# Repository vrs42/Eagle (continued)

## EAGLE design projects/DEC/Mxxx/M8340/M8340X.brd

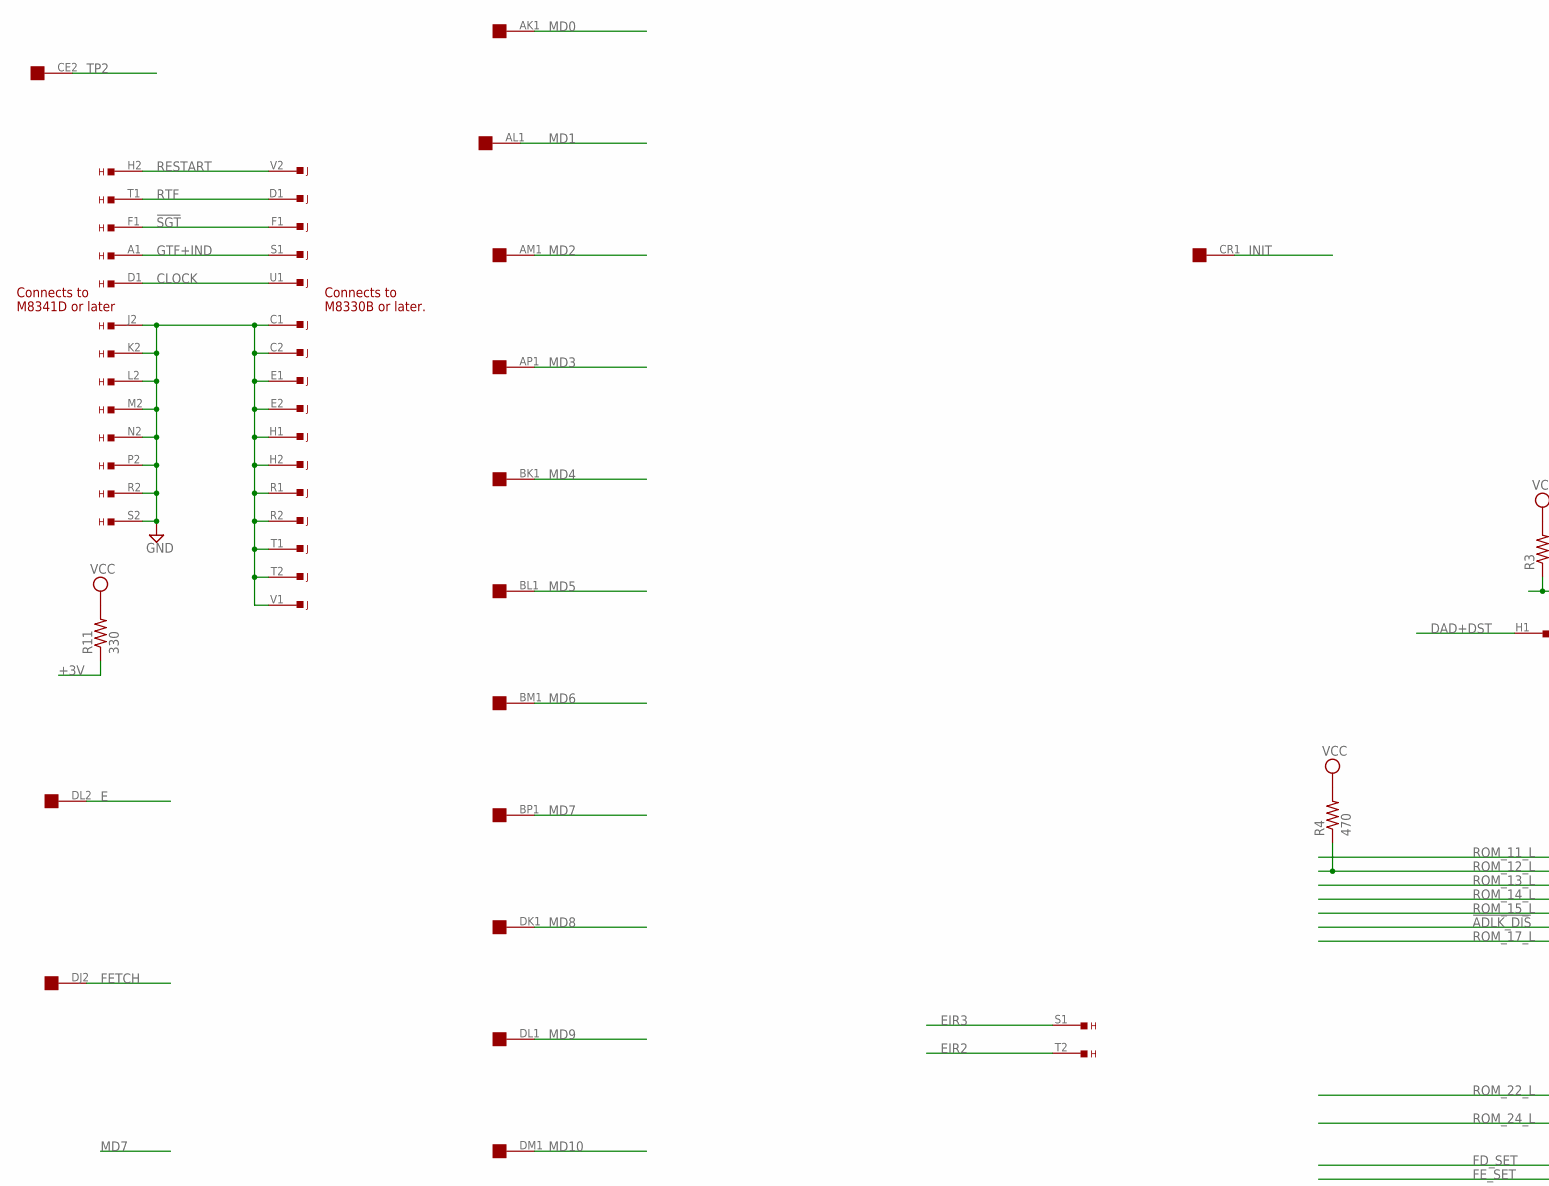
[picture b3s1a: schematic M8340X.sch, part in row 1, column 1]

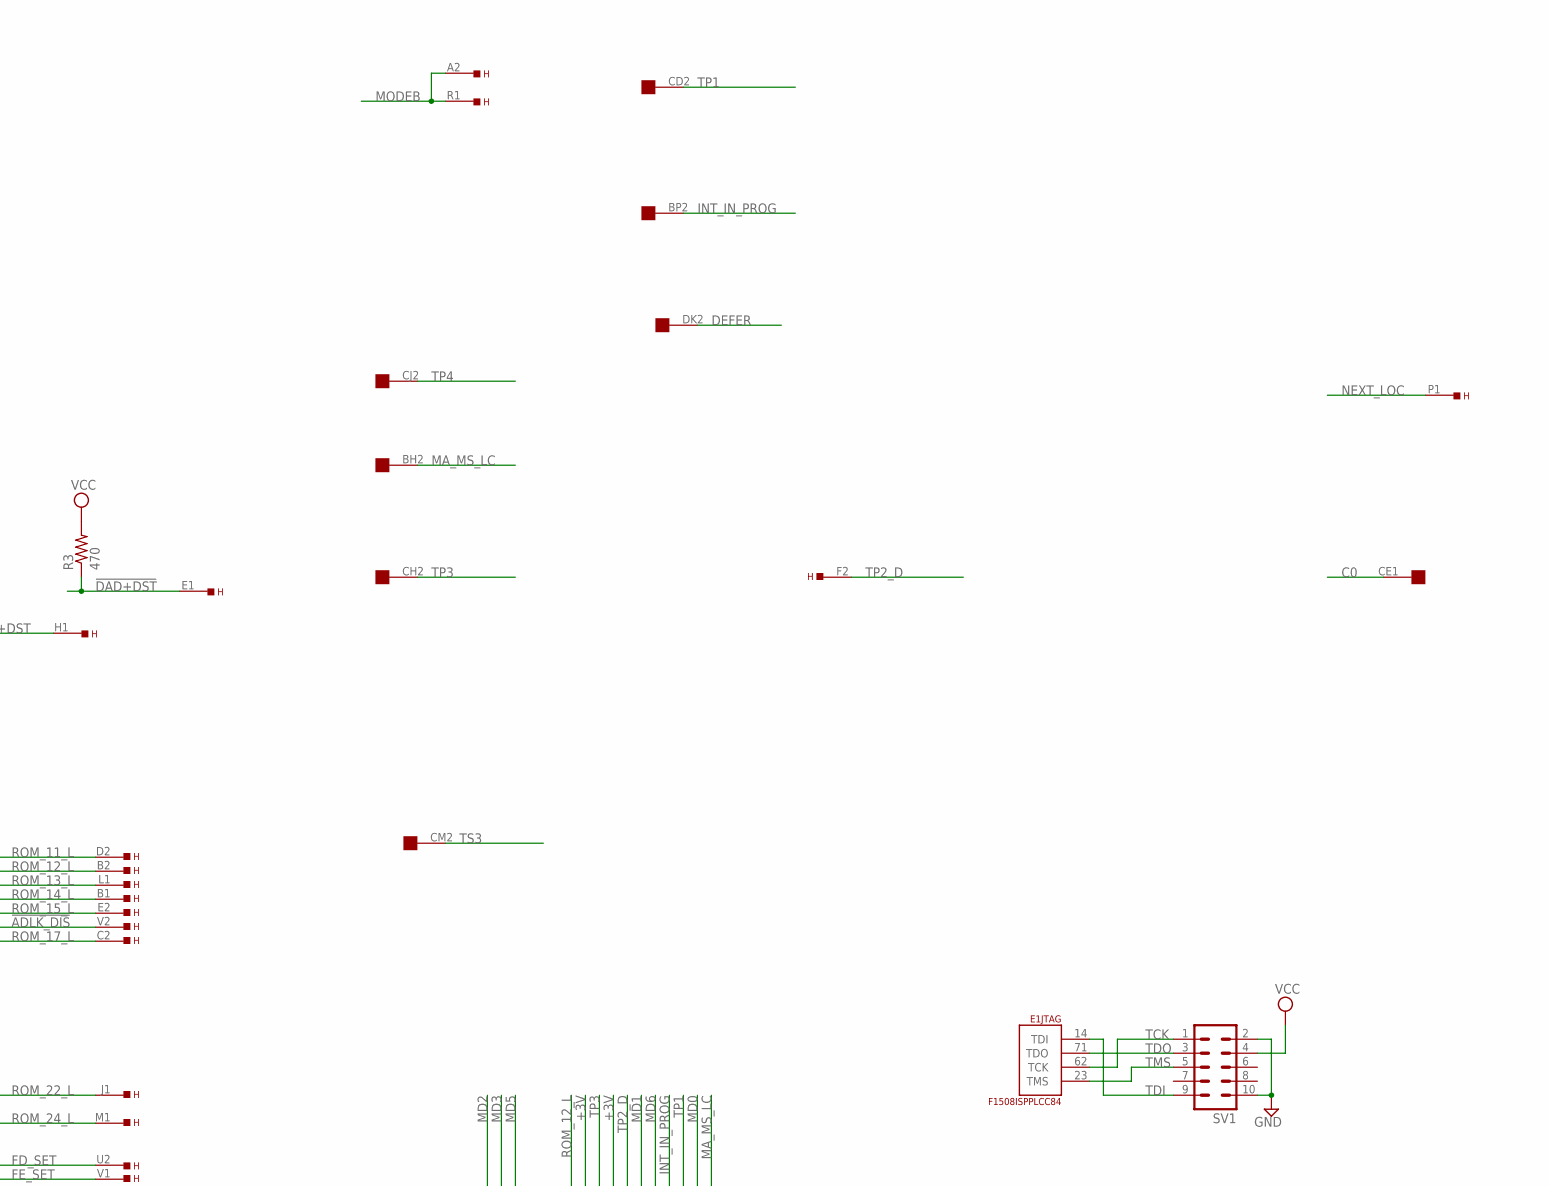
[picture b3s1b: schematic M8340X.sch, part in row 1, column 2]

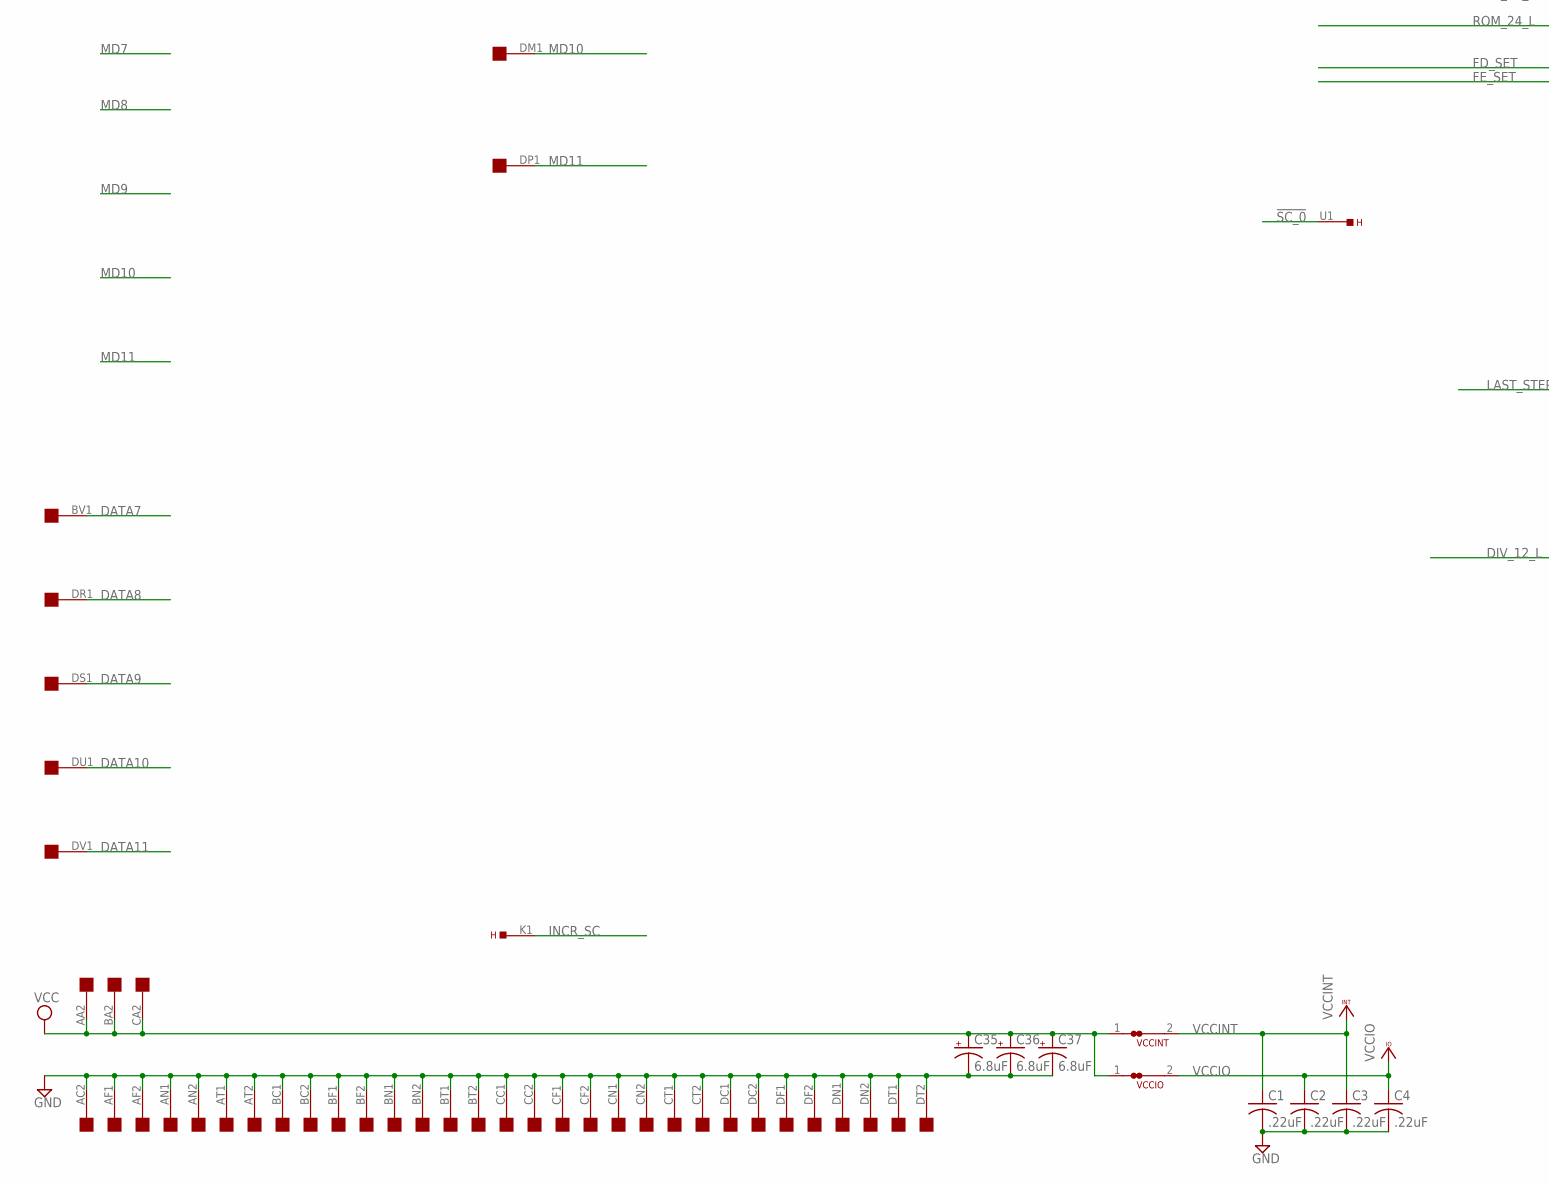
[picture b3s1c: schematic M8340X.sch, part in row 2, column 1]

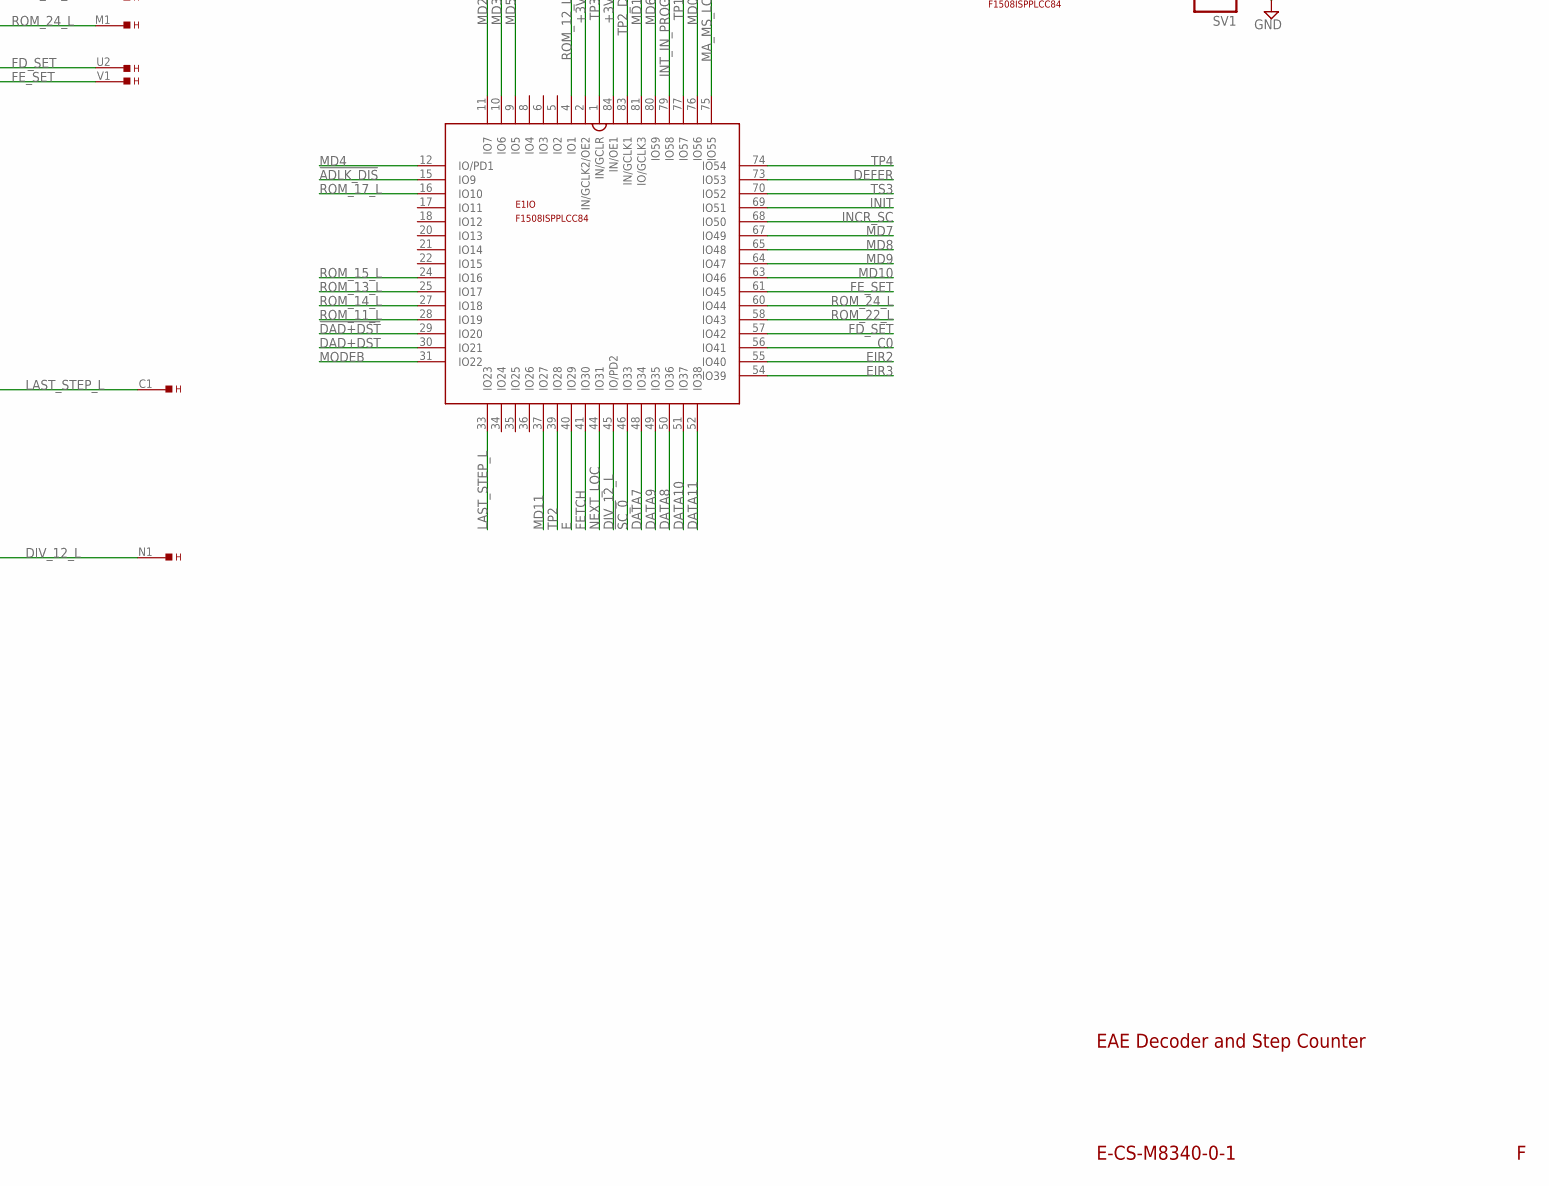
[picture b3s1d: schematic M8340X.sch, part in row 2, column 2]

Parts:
C1, C2, C3, C4: .22uF; C063-025X075
C35, C36, C37: 6.8uF; E12-8
E1: F1508ISPPLCC84; S84
H: EDGE-TOP; EDGE-CON2
J: EDGE-TOP; EDGE-CON2
R3, R4: 470; 0207/10
R11: 330; 0207/10
SV1: ML10
U$2: QUAD; EDGE-CON8
VCCINT: JUMPER-NC1; NC1
VCCIO: JUMPER-NC1; NC1

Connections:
!ADLK_DIS: E1.15 (IO9), H.V2
!DAD+DST: E1.29 (IO20), H.E1, R3.1
!SC_0: E1.46 (IO33), H.U1
!SGT: H.F1, J.F1
+3V: E1.2 (IN/GCLK2/OE2), E1.84 (IN/OE1), R11.1
C0: E1.56 (IO41), U$2.CE1
CLOCK: H.D1, J.U1
DAD+DST: E1.30 (IO21), H.H1
DATA7: E1.48 (IO34), U$2.BV1
DATA8: E1.50 (IO36), U$2.DR1
DATA9: E1.49 (IO35), U$2.DS1
DATA10: E1.51 (IO37), U$2.DU1
DATA11: E1.52 (IO38), U$2.DV1
DEFER: E1.73 (IO53), U$2.DK2
DIV_12_L: E1.45 (IO/PD2), H.N1
E: E1.40 (IO29), U$2.DL2
EIR2: E1.55 (IO40), H.T2
EIR3: E1.54 (IO39), H.S1
FD_SET: E1.57 (IO42), H.U2
FETCH: E1.41 (IO30), U$2.DJ2
FE_SET: E1.61 (IO45), H.V1
GND: C1.2, C2.2, C3.2, C4.2, C35.-, C36.-, C37.-, E1.7 (GND), E1.19 (GND), E1.32 (GND), E1.42 (GND), E1.47 (GND), E1.59 (GND), E1.72 (GND), E1.82 (GND), H.J2, H.K2, H.L2, H.M2, H.N2, H.P2, H.R2, H.S2, J.C1, J.C2, J.E1, J.E2, J.H1, J.H2, J.R1, J.R2, J.T1, J.T2, J.V1, SV1.2, SV1.10, U$2.AC2, U$2.AF1, U$2.AF2, U$2.AN1, U$2.AN2, U$2.AT1, U$2.AT2, U$2.BC1, U$2.BC2, U$2.BF1, U$2.BF2, U$2.BN1, U$2.BN2, U$2.BT1, U$2.BT2, U$2.CC1, U$2.CC2, U$2.CF1, U$2.CF2, U$2.CN1, U$2.CN2, U$2.CT1, U$2.CT2, U$2.DC1, U$2.DC2, U$2.DF1, U$2.DF2, U$2.DN1, U$2.DN2, U$2.DT1, U$2.DT2
GTF+IND: H.A1, J.S1
INCR_SC: E1.68 (IO50), H.K1
INIT: E1.69 (IO51), U$2.CR1
INT_IN_PROG: E1.79 (IO58), U$2.BP2
LAST_STEP_L: E1.33 (IO23), H.C1
MA_MS_LC: E1.75 (IO55), U$2.BH2
MD0: E1.76 (IO56), U$2.AK1
MD1: E1.81 (IO/GCLK3), U$2.AL1
MD2: E1.11 (IO7), U$2.AM1
MD3: E1.10 (IO6), U$2.AP1
MD4: E1.12 (IO/PD1), U$2.BK1
MD5: E1.9 (IO5), U$2.BL1
MD6: E1.80 (IO59), U$2.BM1
MD7: E1.67 (IO49), U$2.BP1
MD8: E1.65 (IO48), U$2.DK1
MD9: E1.64 (IO47), U$2.DL1
MD10: E1.63 (IO46), U$2.DM1
MD11: E1.37 (IO27), U$2.DP1
MODEB: E1.31 (IO22), H.A2, H.R1
NEXT_LOC: E1.44 (IO31), H.P1
RESTART: H.H2, J.V2
ROM_11_L: E1.28 (IO19), H.D2
ROM_12_L: E1.4 (IO1), H.B2, R4.1
ROM_13_L: E1.25 (IO17), H.L1
ROM_14_L: E1.27 (IO18), H.B1
ROM_15_L: E1.24 (IO16), H.E2
ROM_17_L: E1.16 (IO10), H.C2
ROM_22_L: E1.58 (IO43), H.J1
ROM_24_L: E1.60 (IO44), H.M1
RTF: H.T1, J.D1
TCK: E1.62 (TCK), SV1.1
TDI: E1.14 (TDI), SV1.9
TDO: E1.71 (TDO), SV1.3
TMS: E1.23 (TMS), SV1.5
TP1: E1.77 (IO57), U$2.CD2
TP2: E1.39 (IO28), U$2.CE2
TP2_D: E1.83 (IN/GCLK1), H.F2
TP3: E1.1 (IN/GCLR), U$2.CH2
TP4: E1.74 (IO54), U$2.CJ2
TS3: E1.70 (IO52), U$2.CM2
VCC: C35.+, C36.+, C37.+, R3.2, R4.2, R11.2, SV1.4, U$2.AA2, U$2.BA2, U$2.CA2, VCCINT.1, VCCIO.1
VCCINT: C1.1, C3.1, E1.3 (VCCINT), E1.43 (VCCINT), VCCINT.2
VCCIO: C2.1, C4.1, E1.13 (VCCIO), E1.26 (VCCIO), E1.38 (VCCIO), E1.53 (VCCIO), E1.66 (VCCIO), E1.78 (VCCIO), VCCIO.2

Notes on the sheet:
E-CS-M8340-0-1
EAE Decoder and Step Counter
M8330B or later.
Connects to
M8341D or later

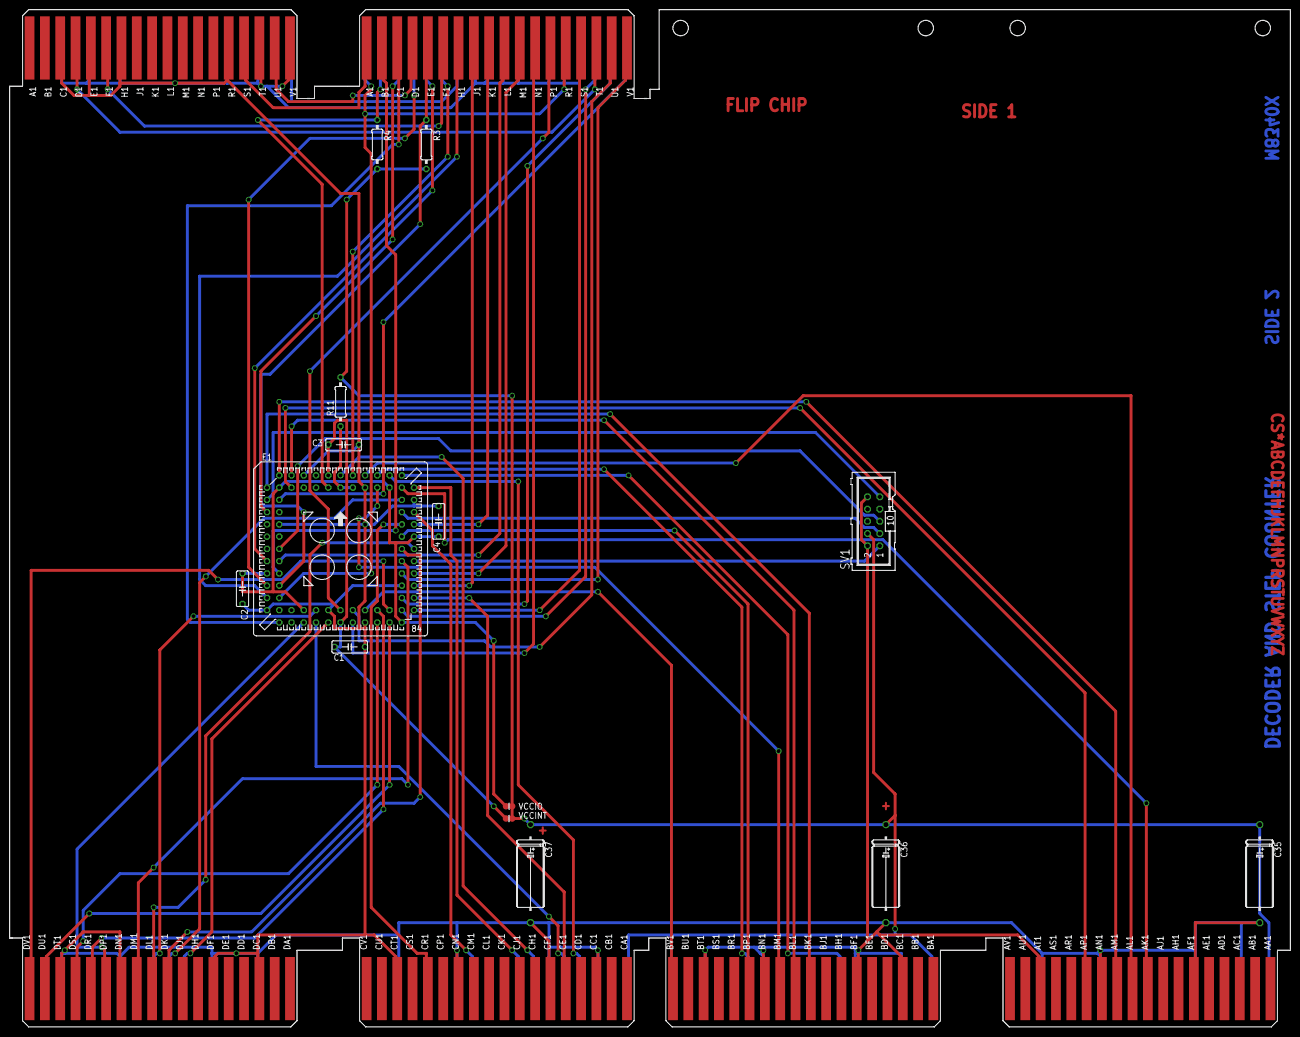
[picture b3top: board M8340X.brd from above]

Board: 2 copper layers, 265.4 x 210.8 mm, 17 parts (0 on the bottom side), 65 nets.

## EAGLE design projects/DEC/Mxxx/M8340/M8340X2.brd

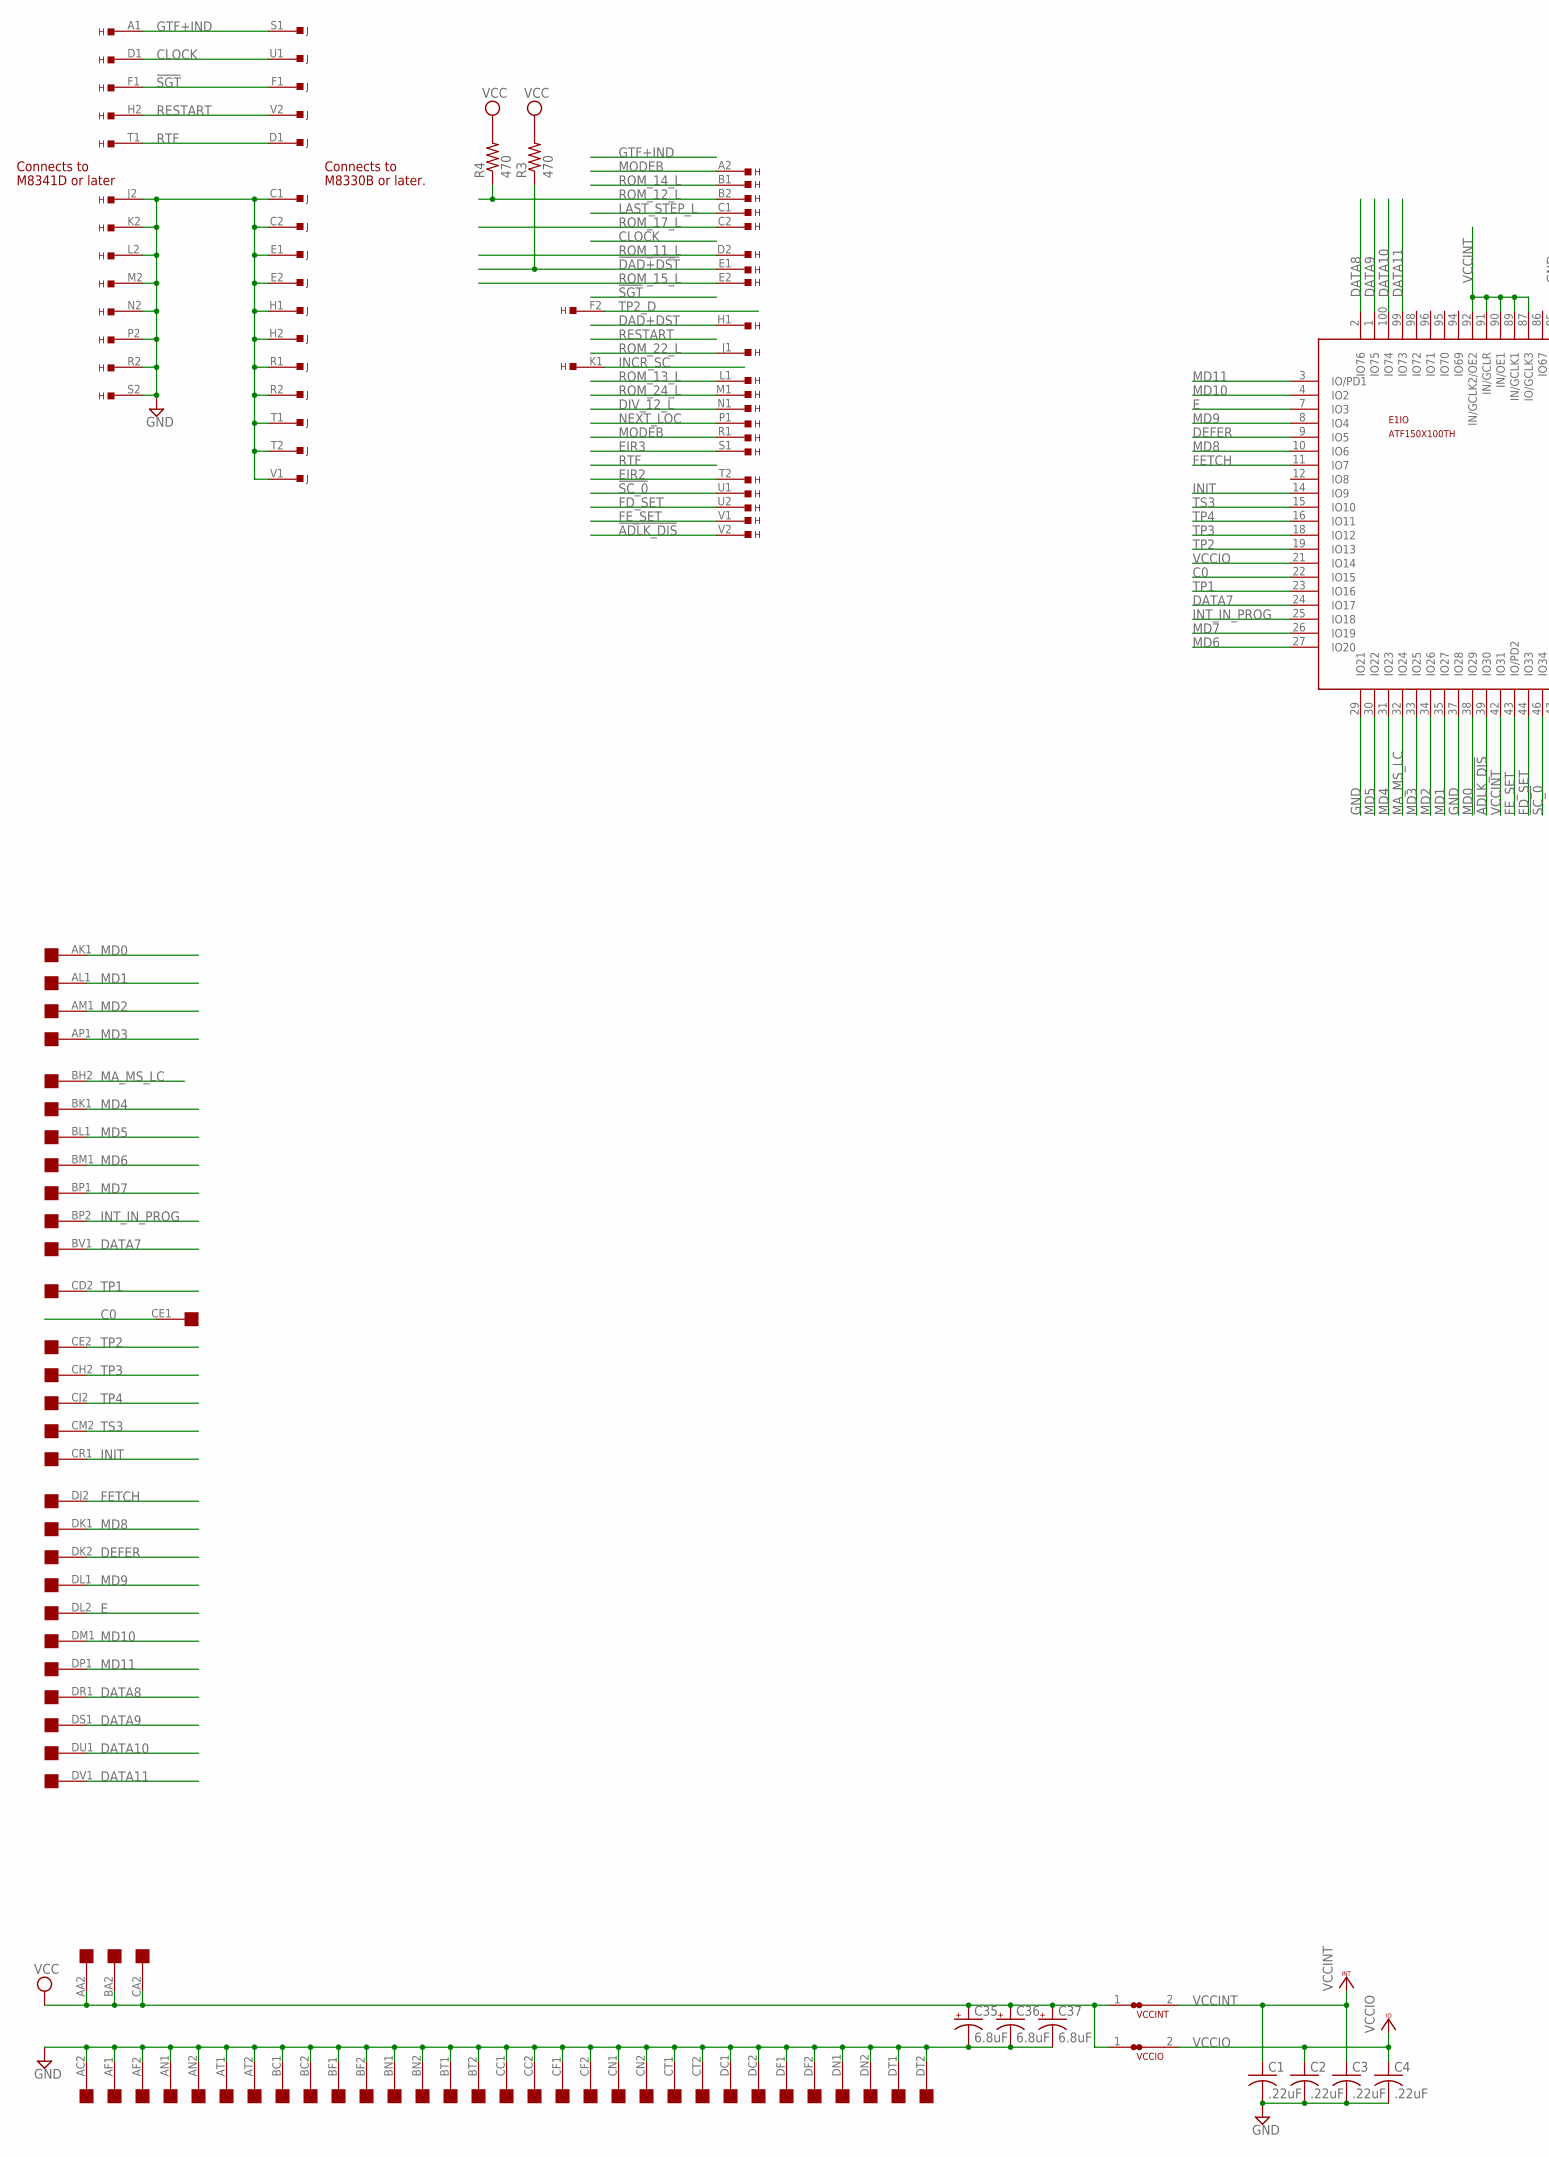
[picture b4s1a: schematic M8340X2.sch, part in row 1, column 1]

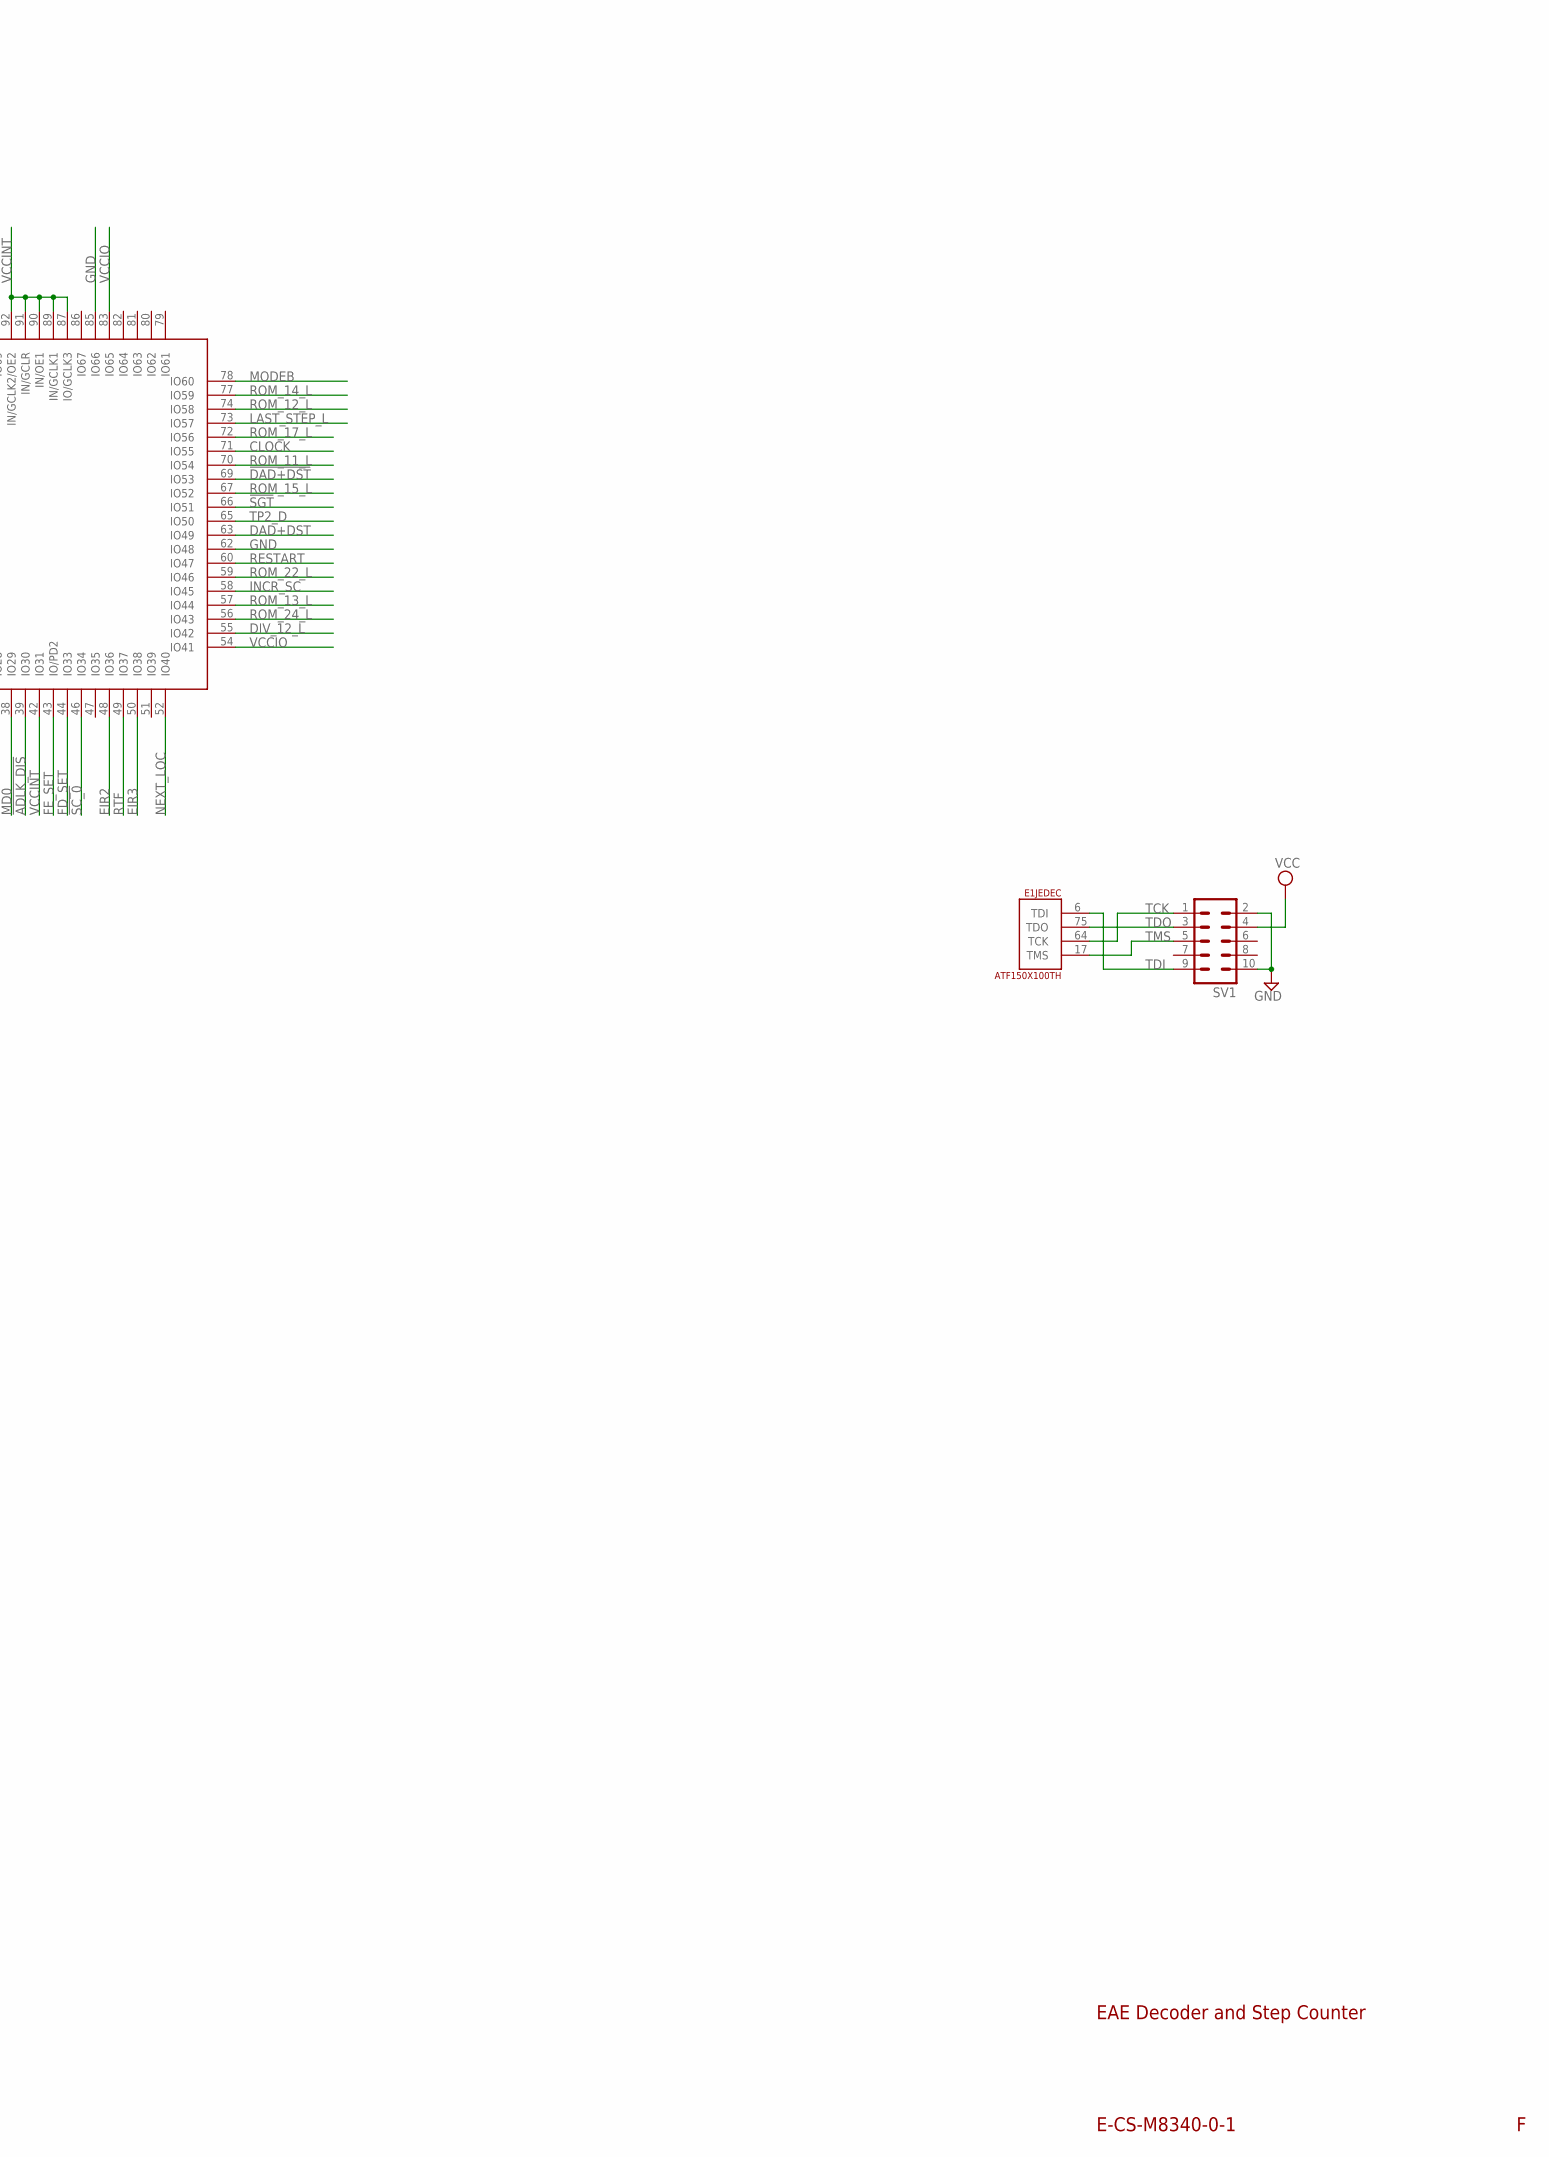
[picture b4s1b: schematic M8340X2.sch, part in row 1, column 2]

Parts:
C1, C2, C3, C4: .22uF; C063-025X075
C35, C36, C37: 6.8uF; E12-8
E1: ATF150X100TH; TH-100
H: EDGE-TOP; EDGE-CON2
J: EDGE-TOP; EDGE-CON2
R3, R4: 470; 0207/10
SV1: ML10
U$1: QUAD; EDGE-CON8
VCCINT: JUMPER-NC1; NC1
VCCIO: JUMPER-NC1; NC1

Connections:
!ADLK_DIS: E1.39 (IO30), H.V2
!DAD+DST: E1.69 (IO53), H.E1, R3.1
!SC_0: E1.46 (IO34), H.U1
!SGT: E1.66 (IO51), H.F1, J.F1
C0: E1.22 (IO15), U$1.CE1
CLOCK: E1.71 (IO55), H.D1, J.U1
DAD+DST: E1.63 (IO49), H.H1
DATA7: E1.24 (IO17), U$1.BV1
DATA8: E1.2 (IO76), U$1.DR1
DATA9: E1.1 (IO75), U$1.DS1
DATA10: E1.100 (IO74), U$1.DU1
DATA11: E1.99 (IO73), U$1.DV1
DEFER: E1.9 (IO5), U$1.DK2
DIV_12_L: E1.55 (IO42), H.N1
E: E1.7 (IO3), U$1.DL2
EIR2: E1.48 (IO36), H.T2
EIR3: E1.50 (IO38), H.S1
FD_SET: E1.44 (IO33), H.U2
FETCH: E1.11 (IO7), U$1.DJ2
FE_SET: E1.43 (IO/PD2), H.V1
GND: C1.2, C2.2, C3.2, C4.2, C35.-, C36.-, C37.-, E1.13 (GND), E1.28 (GND), E1.29 (IO21), E1.37 (IO28), E1.40 (GND), E1.45 (GND), E1.61 (GND), E1.62 (IO48), E1.76 (GND), E1.85 (IO66), E1.88 (GND), E1.97 (GND), H.J2, H.K2, H.L2, H.M2, H.N2, H.P2, H.R2, H.S2, J.C1, J.C2, J.E1, J.E2, J.H1, J.H2, J.R1, J.R2, J.T1, J.T2, J.V1, SV1.2, SV1.10, U$1.AC2, U$1.AF1, U$1.AF2, U$1.AN1, U$1.AN2, U$1.AT1, U$1.AT2, U$1.BC1, U$1.BC2, U$1.BF1, U$1.BF2, U$1.BN1, U$1.BN2, U$1.BT1, U$1.BT2, U$1.CC1, U$1.CC2, U$1.CF1, U$1.CF2, U$1.CN1, U$1.CN2, U$1.CT1, U$1.CT2, U$1.DC1, U$1.DC2, U$1.DF1, U$1.DF2, U$1.DN1, U$1.DN2, U$1.DT1, U$1.DT2
GTF+IND: H.A1, J.S1
INCR_SC: E1.58 (IO45), H.K1
INIT: E1.14 (IO9), U$1.CR1
INT_IN_PROG: E1.25 (IO18), U$1.BP2
LAST_STEP_L: E1.73 (IO57), H.C1
MA_MS_LC: E1.32 (IO24), U$1.BH2
MD0: E1.38 (IO29), U$1.AK1
MD1: E1.35 (IO27), U$1.AL1
MD2: E1.34 (IO26), U$1.AM1
MD3: E1.33 (IO25), U$1.AP1
MD4: E1.31 (IO23), U$1.BK1
MD5: E1.30 (IO22), U$1.BL1
MD6: E1.27 (IO20), U$1.BM1
MD7: E1.26 (IO19), U$1.BP1
MD8: E1.10 (IO6), U$1.DK1
MD9: E1.8 (IO4), U$1.DL1
MD10: E1.4 (IO2), U$1.DM1
MD11: E1.3 (IO/PD1), U$1.DP1
MODEB: E1.78 (IO60), H.A2, H.R1
NEXT_LOC: E1.52 (IO40), H.P1
RESTART: E1.60 (IO47), H.H2, J.V2
ROM_11_L: E1.70 (IO54), H.D2
ROM_12_L: E1.74 (IO58), H.B2, R4.1
ROM_13_L: E1.57 (IO44), H.L1
ROM_14_L: E1.77 (IO59), H.B1
ROM_15_L: E1.67 (IO52), H.E2
ROM_17_L: E1.72 (IO56), H.C2
ROM_22_L: E1.59 (IO46), H.J1
ROM_24_L: E1.56 (IO43), H.M1
RTF: E1.49 (IO37), H.T1, J.D1
TCK: E1.64 (TCK), SV1.1
TDI: E1.6 (TDI), SV1.9
TDO: E1.75 (TDO), SV1.3
TMS: E1.17 (TMS), SV1.5
TP1: E1.23 (IO16), U$1.CD2
TP2: E1.19 (IO13), U$1.CE2
TP2_D: E1.65 (IO50), H.F2
TP3: E1.18 (IO12), U$1.CH2
TP4: E1.16 (IO11), U$1.CJ2
TS3: E1.15 (IO10), U$1.CM2
VCC: C35.+, C36.+, C37.+, R3.2, R4.2, SV1.4, U$1.AA2, U$1.BA2, U$1.CA2, VCCINT.1, VCCIO.1
VCCINT: C1.1, C3.1, E1.41 (VCCINT), E1.42 (IO31), E1.87 (IO/GCLK3), E1.89 (IN/GCLK1), E1.90 (IN/OE1), E1.91 (IN/GCLR), E1.92 (IN/GCLK2/OE2), E1.93 (VCCINT), VCCINT.2
VCCIO: C2.1, C4.1, E1.5 (VCCIO), E1.20 (VCCIO), E1.21 (IO14), E1.36 (VCCIO), E1.53 (VCCIO), E1.54 (IO41), E1.68 (VCCIO), E1.83 (IO65), E1.84 (VCCIO), VCCIO.2

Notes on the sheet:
E-CS-M8340-0-1
EAE Decoder and Step Counter
M8330B or later.
Connects to
M8341D or later

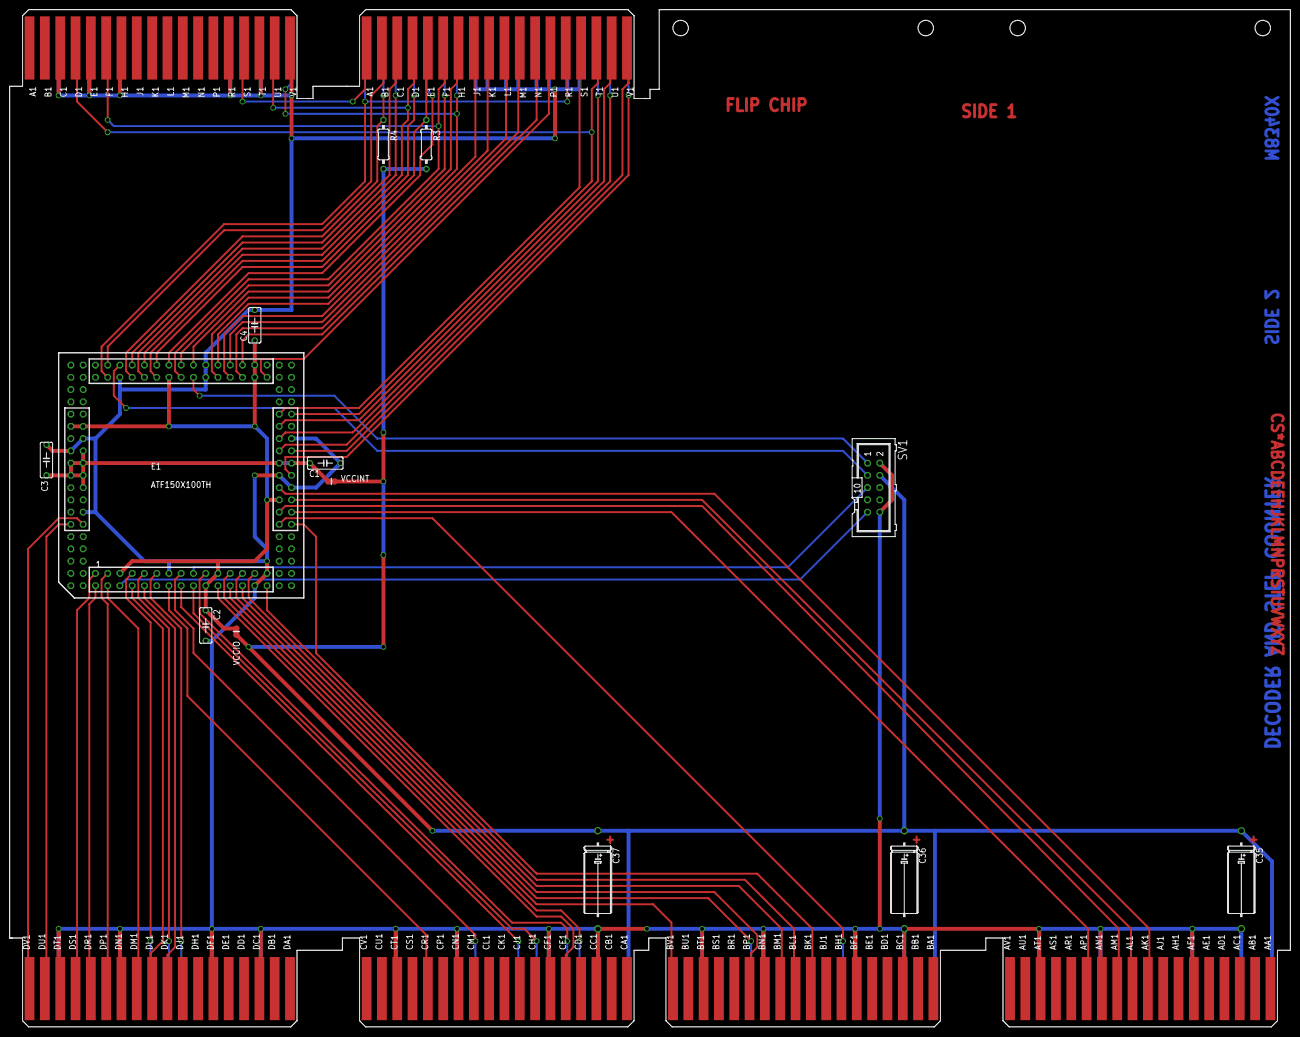
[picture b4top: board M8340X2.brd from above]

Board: 2 copper layers, 265.4 x 210.8 mm, 16 parts (0 on the bottom side), 64 nets.
